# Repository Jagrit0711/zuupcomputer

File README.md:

# Zuup Computer

An open hardware project for a small computer built from discrete transistors, with three seven-segment digits and user-added pushbuttons.

## What is designed now

This first KiCad revision is **Stage 1: a two-input transistor NOR gate**. It is the smallest reusable logic block for the computer. The schematic and routed two-layer PCB use two 2N3904 NPN transistors, resistors, and headers for power, inputs, and output. The board passes KiCad's electrical and board checks. It has not been fabricated or electrically tested yet.

The 8-bit computer and three-digit display are the project goal; they are **not implemented in this first revision**. A full discrete-transistor design needs many repeated logic cells and several rounds of testing before it is safe to order as one large PCB. See [HOW_IT_WORKS.md](HOW_IT_WORKS.md) for the beginner explanation and [ARCHITECTURE.md](ARCHITECTURE.md) for the design plan.

## Open the design

Open `Zuup_Computer.kicad_pro` in KiCad 10. The project schematic is `Zuup_Computer.kicad_sch`, and the routed board is `Zuup_Computer.kicad_pcb`.

The NOR-gate board's Gerbers and drill file are in `fabrication/NOR-v0.1/`. The PDF schematic and 3D board preview are included for quick review.

## Stage 1: NOR gate

The circuit implements:

```text
Y = NOT (A OR B)
```

| A | B | Y |
|---:|---:|---:|
| 0 | 0 | 1 |
| 0 | 1 | 0 |
| 1 | 0 | 0 |
| 1 | 1 | 0 |

Use a regulated **5 V DC** supply. Inputs A and B are logic levels: connect an input to GND for 0 or +5 V for 1. R4 and R5 pull the transistor bases low when the input is open, so a pushbutton can connect each input to +5 V. J1 pin order is `+5V, GND, A, B`; J2 is `Y, GND`.

The schematic uses a 1 kΩ collector pull-up, 10 kΩ base resistors, and 100 kΩ base pull-downs. A 2N3904 footprint is assigned. Check the exact transistor manufacturer's pinout against the board footprint before assembling; different TO-92 parts can have different lead orders.

## Open hardware license

The hardware design files are licensed under **CERN-OHL-S-2.0** so people can study and modify the design, with changes to shared hardware designs kept under the same license. The official text is linked in [LICENSE](LICENSE).

## First-stage parts

See [BOM.csv](BOM.csv) for the part list. Use through-hole parts and 2.54 mm headers so the first prototype is easy to inspect and modify.

## Building toward the computer

1. Assemble and verify the NOR gate at 5 V.
2. Combine NOR gates into a one-bit half adder and then a full adder.
3. Chain eight full-adder cells for an 8-bit addition unit, with a ninth carry output.
4. Add input storage and a result latch so the buttons can enter two numbers and hold the answer.
5. Add a binary-to-decimal conversion stage and three seven-segment driver stages for results from 000 to 255.

The pushbuttons can be added as the front-panel controls in a later revision. Their contacts should connect to defined logic levels, with pull-down resistors so open buttons do not leave inputs floating.

## Safety and build notes

- Keep this low-voltage: use 5 V DC and do not connect mains power.
- Do not order a later computer PCB from this Stage 1 project; only the NOR gate has a component-level schematic here.
- Prototype each logic cell first. Discrete resistor-transistor logic has limited drive strength, so a cell's output fan-out must be checked before it drives several following gates.
# zuupcomputer

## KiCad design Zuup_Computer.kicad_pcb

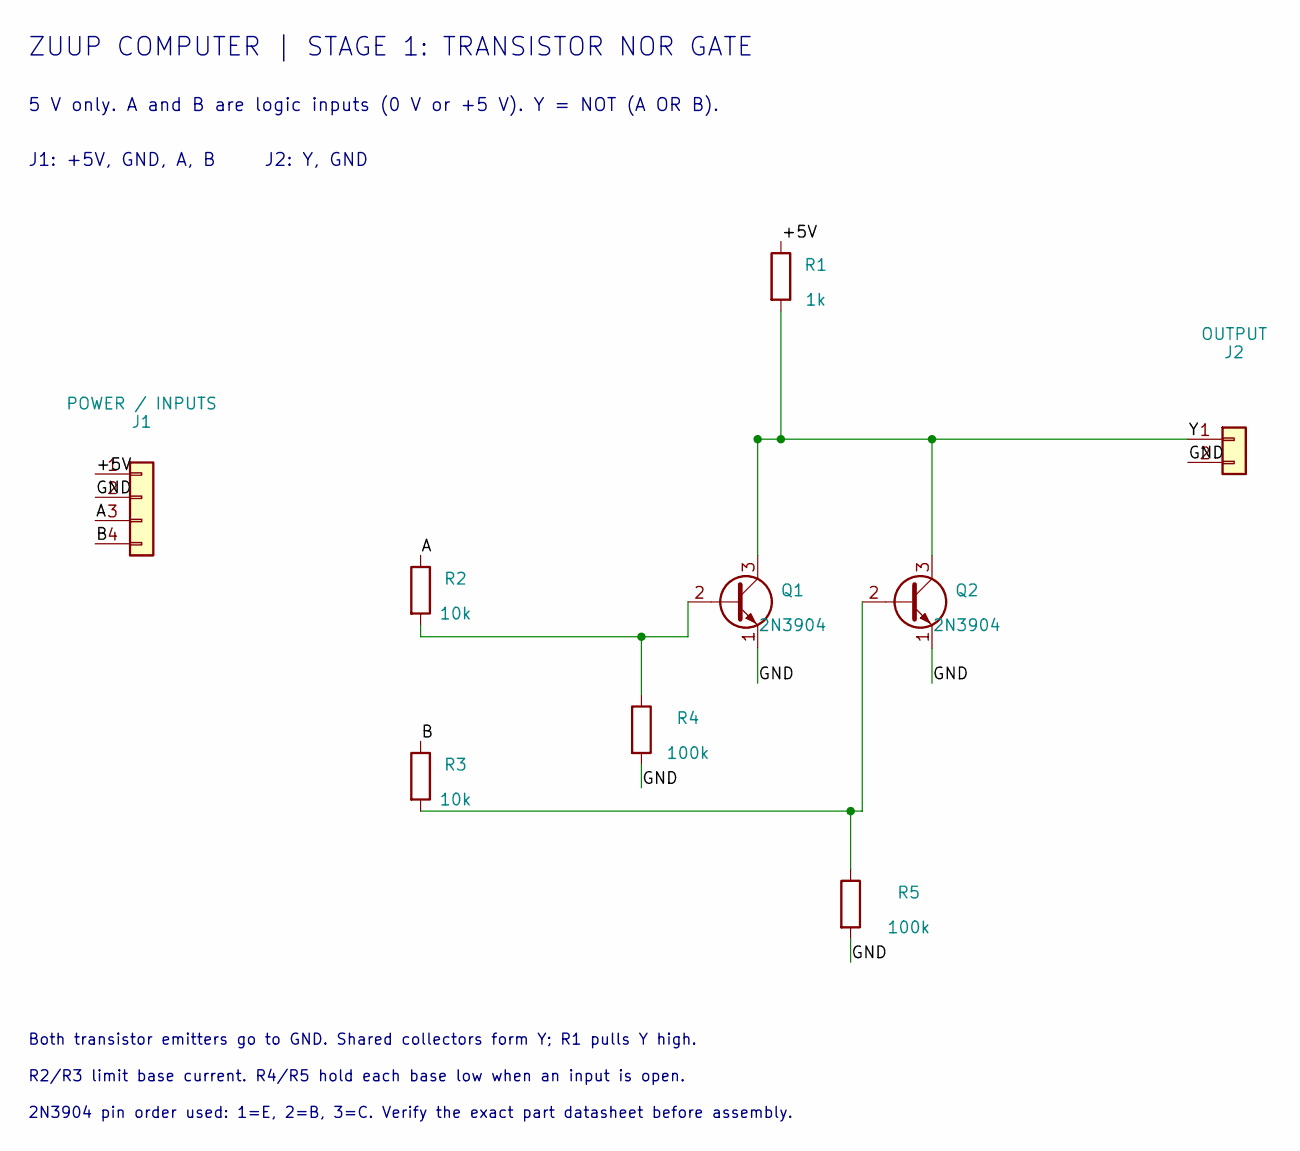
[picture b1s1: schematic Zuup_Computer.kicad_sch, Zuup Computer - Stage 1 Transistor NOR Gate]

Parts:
J1: POWER / INPUTS; PinHeader_1x04_P2.54mm_Vertical
J2: OUTPUT; PinHeader_1x02_P2.54mm_Vertical
Q1, Q2: 2N3904; TO-92_Inline
R1: 1k; R_Axial_DIN0207_L6.3mm_D2.5mm_P10.16mm_Horizontal
R2, R3: 10k; R_Axial_DIN0207_L6.3mm_D2.5mm_P10.16mm_Horizontal
R4, R5: 100k; R_Axial_DIN0207_L6.3mm_D2.5mm_P10.16mm_Horizontal

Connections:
+5V: J1.1, R1.1
A: J1.3, R2.1
A_BASE: Q1.2 (B), R2.2, R4.1
B: J1.4, R3.1
B_BASE: Q2.2 (B), R3.2, R5.1
GND: J1.2, J2.2, Q1.1 (E), Q2.1 (E), R4.2, R5.2
Y: J2.1, Q1.3 (C), Q2.3 (C), R1.2

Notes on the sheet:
ZUUP COMPUTER | STAGE 1: TRANSISTOR NOR GATE
5 V only. A and B are logic inputs (0 V or +5 V). Y = NOT (A OR B).
J1: +5V, GND, A, B J2: Y, GND
Both transistor emitters go to GND. Shared collectors form Y; R1 pulls Y high.
R2/R3 limit base current. R4/R5 hold each base low when an input is open.
2N3904 pin order used: 1=E, 2=B, 3=C. Verify the exact part datasheet before assembly.

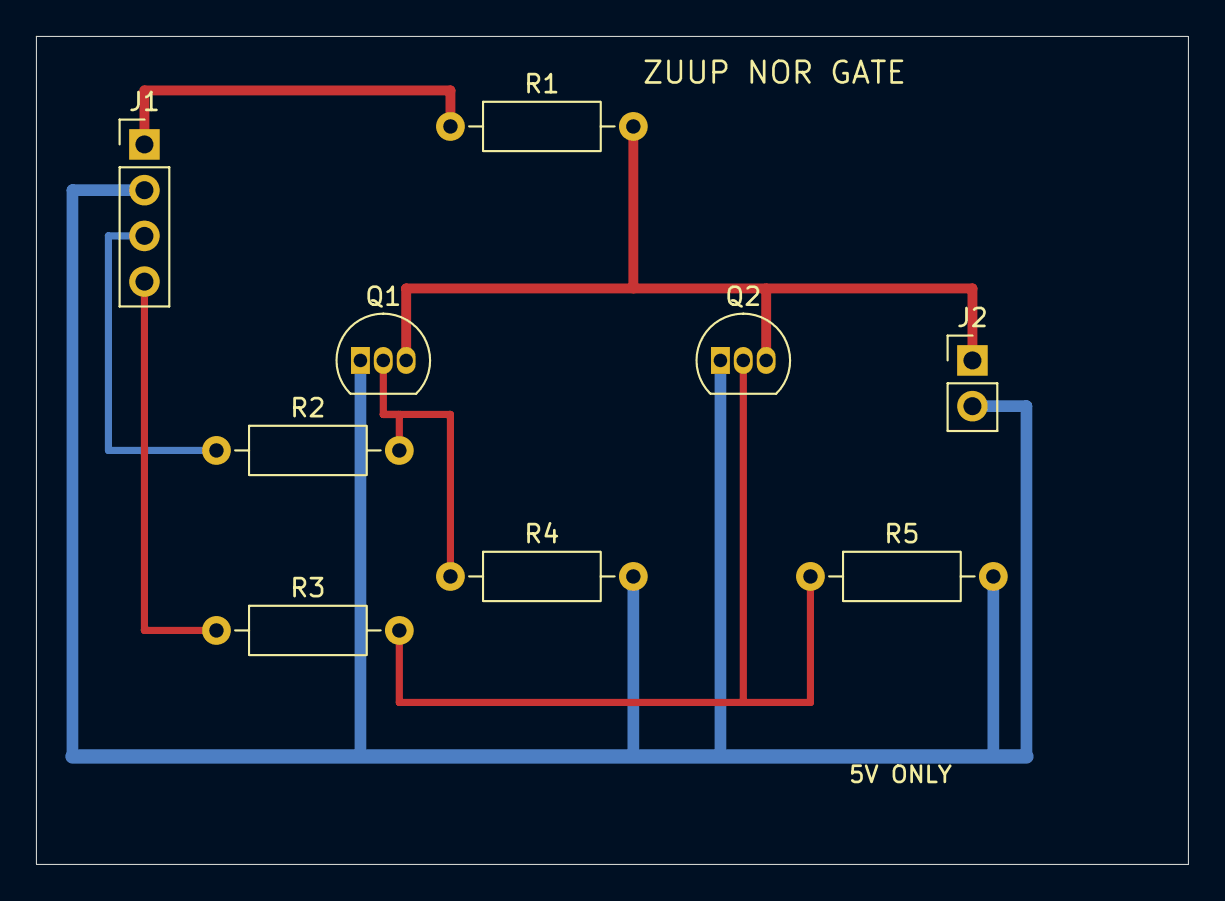
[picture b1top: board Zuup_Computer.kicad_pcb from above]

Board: 2 copper layers, 64.0 x 46.0 mm, 9 parts (0 on the bottom side), 7 nets.

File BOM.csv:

Reference,Quantity,Value / part,Footprint,Notes
Q1-Q2,2,2N3904 NPN,Package_TO_SOT_THT:TO-92_Inline,Check the exact vendor lead order against the footprint before assembly
R1,1,1 kOhm,Resistor_THT:R_Axial_DIN0207_L6.3mm_D2.5mm_P10.16mm_Horizontal,Collector pull-up
R2-R3,2,10 kOhm,Resistor_THT:R_Axial_DIN0207_L6.3mm_D2.5mm_P10.16mm_Horizontal,Base current limiting
R4-R5,2,100 kOhm,Resistor_THT:R_Axial_DIN0207_L6.3mm_D2.5mm_P10.16mm_Horizontal,Base pull-down
J1,1,1x4 2.54 mm pin header,Connector_PinHeader_2.54mm:PinHeader_1x04_P2.54mm_Vertical,Pin order +5V GND A B
J2,1,1x2 2.54 mm pin header,Connector_PinHeader_2.54mm:PinHeader_1x02_P2.54mm_Vertical,Pin order Y GND
